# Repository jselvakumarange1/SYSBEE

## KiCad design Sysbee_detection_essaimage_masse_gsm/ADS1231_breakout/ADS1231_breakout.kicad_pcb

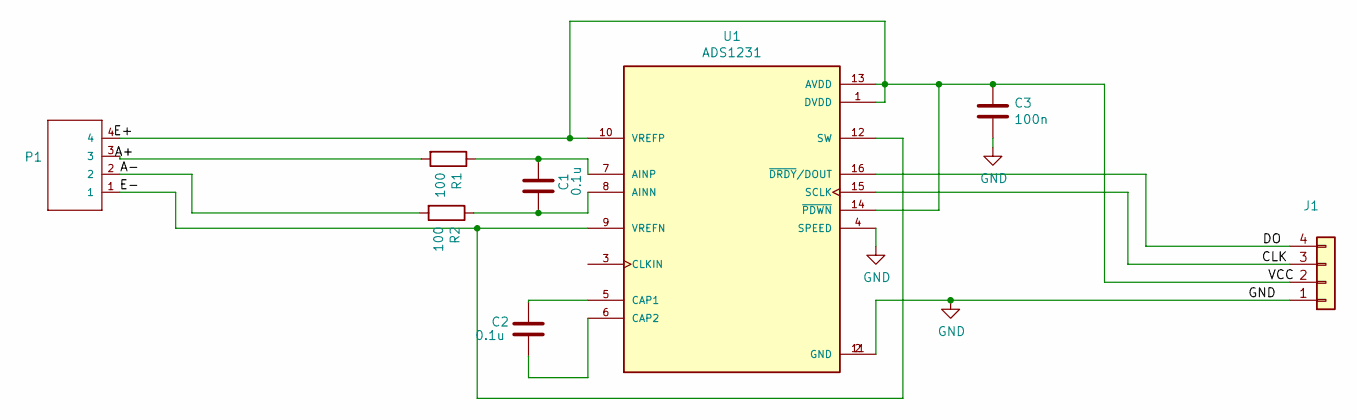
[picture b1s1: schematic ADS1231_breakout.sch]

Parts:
C1: 0.1u; C_1206_3216Metric
C2: 0.1u; C_1210_3225Metric
C3: 100n; C_1210_3225Metric
J1: FanPinHeader_1x04_P2.54mm_Vertical
P1: FanPinHeader_1x04_P2.54mm_Vertical
R1, R2: 100; R_1206_3216Metric
U1: ADS1231; SO-16_3.9x9.9mm_P1.27mm

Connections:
/A+: P1.3, R1.2
/A-: P1.2, R2.2
/CLK: J1.3, U1.15 (SCLK)
/DO: J1.4, U1.16 (~DRDY~/DOUT)
/E+: C3.1, J1.2, P1.4, U1.1 (DVDD), U1.10 (VREFP), U1.13 (AVDD), U1.14 (~PDWN)
/E-: P1.1, U1.9 (VREFN), U1.12 (SW)
GND: C3.2, J1.1, U1.2 (GND), U1.4 (SPEED), U1.11 (GND)
unnamed: C1.1, R1.1, U1.7 (AINP)
unnamed: C1.2, R2.1, U1.8 (AINN)
unnamed: C2.1, U1.5 (CAP1)
unnamed: C2.2, U1.6 (CAP2)

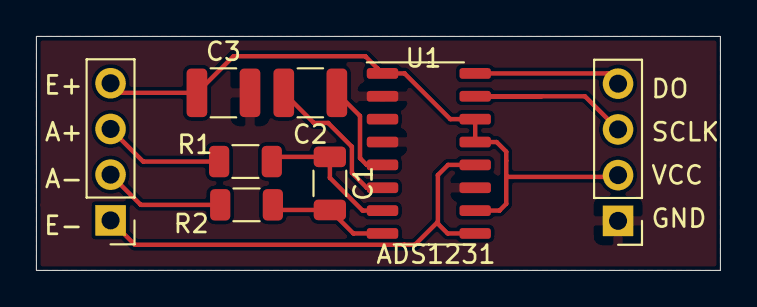
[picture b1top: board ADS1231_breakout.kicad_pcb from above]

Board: 2 copper layers, 38.0 x 13.0 mm, 8 parts (0 on the bottom side), 11 nets.

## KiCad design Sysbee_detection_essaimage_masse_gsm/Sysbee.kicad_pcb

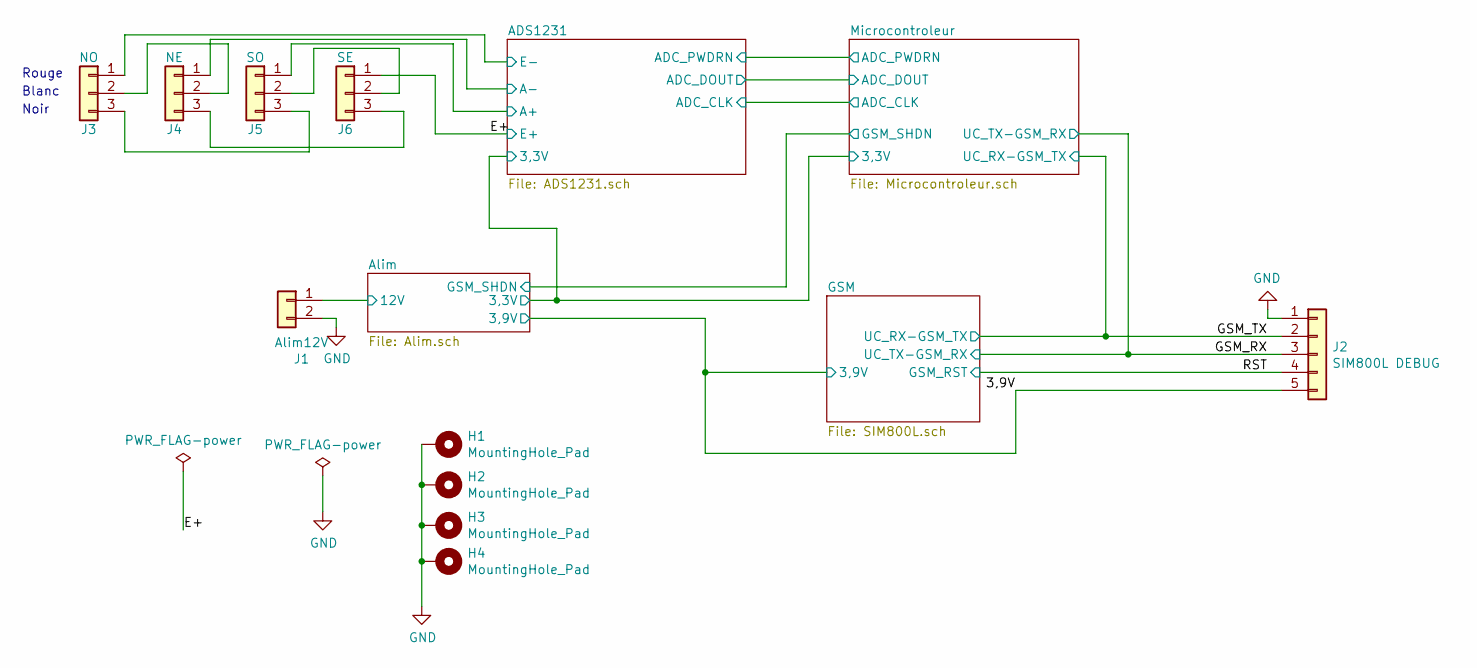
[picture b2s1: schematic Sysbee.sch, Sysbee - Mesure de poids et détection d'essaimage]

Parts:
H1, H2, H3, H4: MountingHole_Pad; Arduino_1pin
J1: Alim12V; PhoenixContact_MC_1,5_2-G-3.5_1x02_P3.50mm_Horizontal
J2: SIM800L DEBUG; PinHeader_1x05_P2.54mm_Vertical
J3: NO; JST_PH_B3B-PH-K_1x03_P2.00mm_Vertical
J4: NE; JST_PH_B3B-PH-K_1x03_P2.00mm_Vertical
J5: SO; JST_PH_B3B-PH-K_1x03_P2.00mm_Vertical
J6: SE; JST_PH_B3B-PH-K_1x03_P2.00mm_Vertical

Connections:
/3,9V: J2.5; also elsewhere on the board
/ADS1231/A+: J5.1; also elsewhere on the board
/ADS1231/A-: J4.1; also elsewhere on the board
/ADS1231/E-: J3.1; also elsewhere on the board
/Alim/12V: J1.1; also elsewhere on the board
/E+: J6.1; also elsewhere on the board
/GSM_RX: J2.3; also elsewhere on the board
/GSM_TX: J2.2; also elsewhere on the board
/RST: J2.4; also elsewhere on the board
GND: H1.1, H2.1, H3.1, H4.1, J1.2, J2.1; also elsewhere on the board
unnamed: J3.2, J4.2
unnamed: J3.3, J5.3
unnamed: J4.3, J6.3
unnamed: J5.2, J6.2

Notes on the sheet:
Rouge
Blanc
Noir

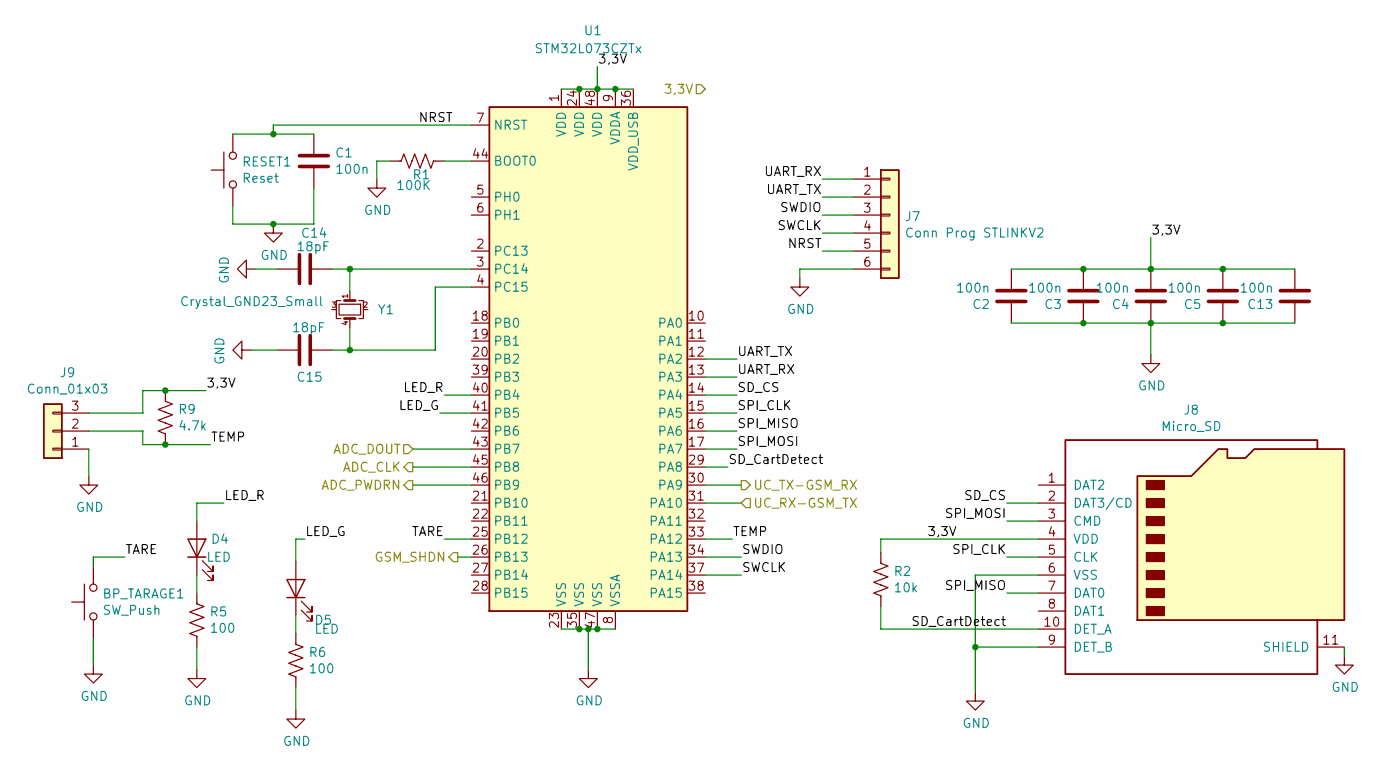
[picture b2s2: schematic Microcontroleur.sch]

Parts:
BP_TARAGE1: SW_Push; SW_SPST_TL3305C
C1, C2, C3, C4, C5, C13: 100n; C_1206_3216Metric
C14, C15: 18pF; C_0805_2012Metric
D4, D5: LED; LED_1206_3216Metric
J7: Conn Prog STLINKV2; Micro-match_6
J8: Micro_SD; 504077-1891
J9: Conn_01x03; JST_PH_B3B-PH-K_1x03_P2.00mm_Vertical
R1: 100K; R_1206_3216Metric
R2: 10k; R_1206_3216Metric
R5, R6: 100; R_1206_3216Metric
R9: 4.7k; R_1206_3216Metric
RESET1: Reset; SW_SPST_TL3305C
U1: STM32L073CZTx; LQFP-48_7x7mm_P0.5mm
Y1: Crystal_GND23_Small; Crystal_SMD_SeikoEpson_MC156-4Pin_7.1x2.5mm

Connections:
/ADS1231/ADC_CLK: U1.45 (PB8); also elsewhere on the board
/ADS1231/ADC_DOUT: U1.43 (PB7); also elsewhere on the board
/ADS1231/ADC_PWDRN: U1.46 (PB9); also elsewhere on the board
/Alim/GSM_SHDN: U1.26 (PB13); also elsewhere on the board
/E+: C2.2, C3.2, C4.2, C5.2, C13.2, J8.4 (VDD), J9.3, R2.1, R9.1, U1.1 (VDD), U1.9 (VDDA), U1.24 (VDD), U1.36 (VDD_USB), U1.48 (VDD); also elsewhere on the board
/GSM_RX: U1.30 (PA9); also elsewhere on the board
/GSM_TX: U1.31 (PA10); also elsewhere on the board
/Microcontroleur/LED_G: D5.2 (A), U1.41 (PB5)
/Microcontroleur/LED_R: D4.2 (A), U1.40 (PB4)
/Microcontroleur/NRST: C1.1, J7.5, RESET1.2, U1.7 (NRST)
/Microcontroleur/SD_CS: J8.2 (DAT3/CD), U1.14 (PA4)
/Microcontroleur/SD_CartDetect: J8.10 (DET_A), R2.2, U1.29 (PA8)
/Microcontroleur/SPI_CLK: J8.5 (CLK), U1.15 (PA5)
/Microcontroleur/SPI_MISO: J8.7 (DAT0), U1.16 (PA6)
/Microcontroleur/SPI_MOSI: J8.3 (CMD), U1.17 (PA7)
/Microcontroleur/SWCLK: J7.4, U1.37 (PA14)
/Microcontroleur/SWDIO: J7.3, U1.34 (PA13)
/Microcontroleur/TARE: BP_TARAGE1.2, U1.25 (PB12)
/Microcontroleur/TEMP: J9.2, R9.2, U1.33 (PA12)
/Microcontroleur/UART_RX: J7.1, U1.13 (PA3)
/Microcontroleur/UART_TX: J7.2, U1.12 (PA2)
GND: BP_TARAGE1.1, C1.2, C2.1, C3.1, C4.1, C5.1, C13.1, C14.2, C15.2, J7.6, J8.6 (VSS), J8.9 (DET_B), J8.11 (SHIELD), J9.1, R1.1, R5.2, R6.2, RESET1.1, U1.8 (VSSA), U1.23 (VSS), U1.35 (VSS), U1.47 (VSS); also elsewhere on the board
unnamed: C14.1, U1.3 (PC14), Y1.1
unnamed: C15.1, U1.4 (PC15), Y1.4
unnamed: D4.1 (K), R5.1
unnamed: D5.1 (K), R6.1
unnamed: R1.2, U1.44 (BOOT0)

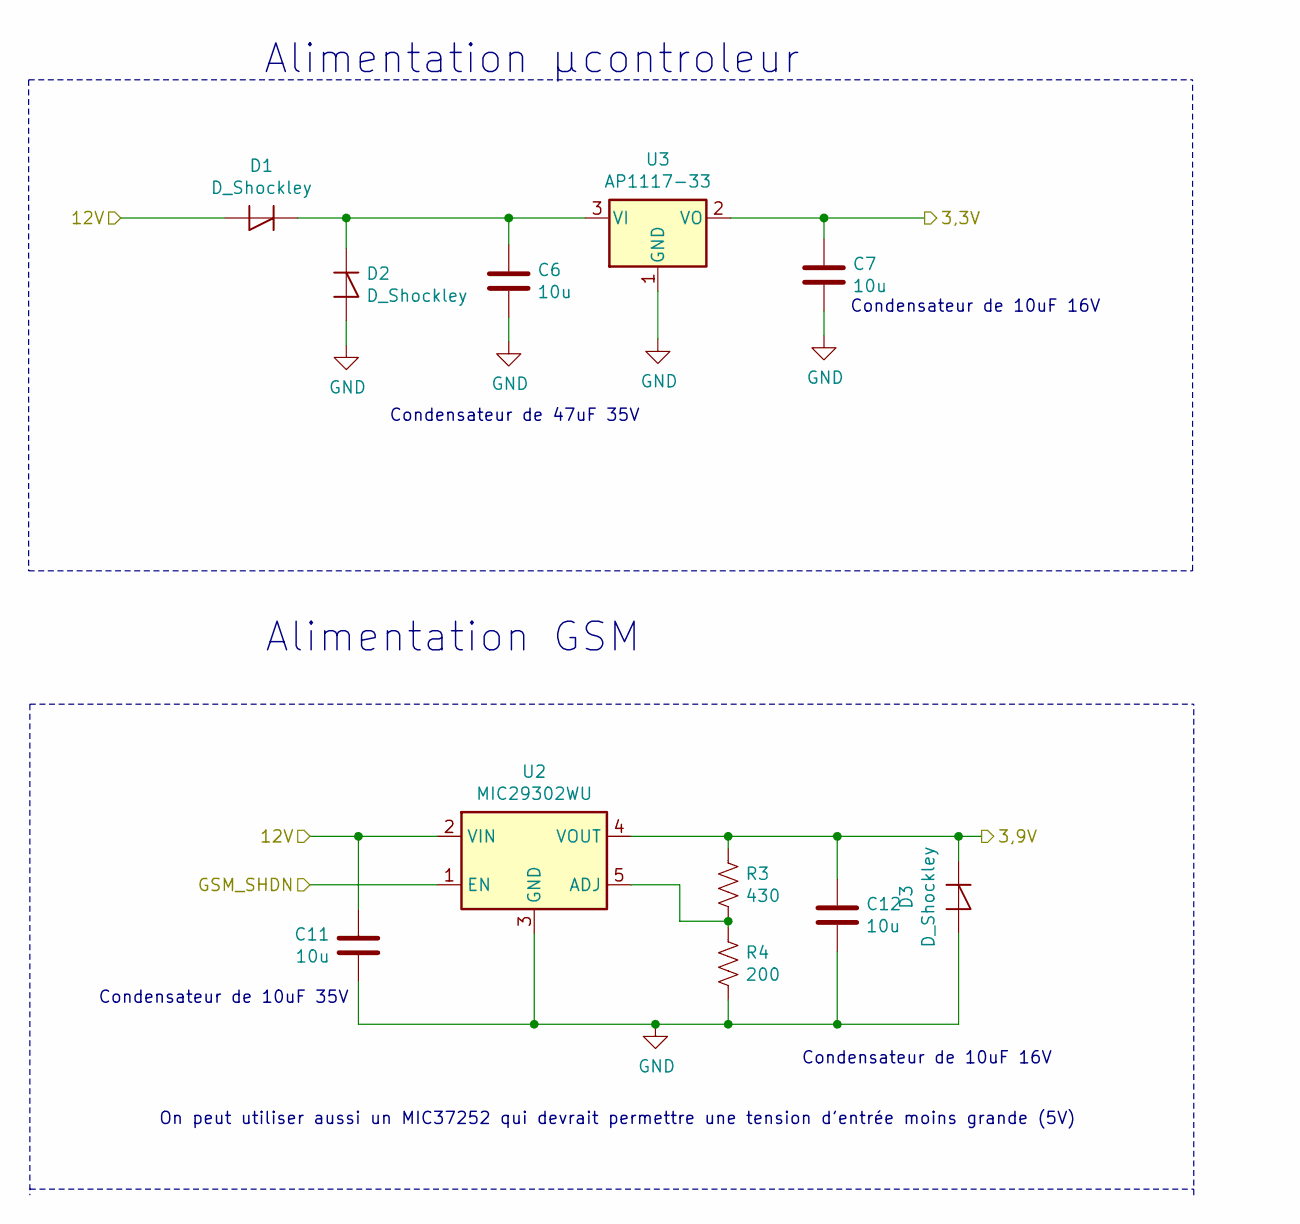
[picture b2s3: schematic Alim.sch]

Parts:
C6, C11: 10u; CP_EIA-6032-15_Kemet-U
C7, C12: 10u; CP_EIA-3528-21_Kemet-B
D1, D2, D3: D_Shockley; D_SOD-123
R3: 430; R_1206_3216Metric
R4: 200; R_1206_3216Metric
U2: MIC29302WU; TO-263-5_TabPin3
U3: AP1117-33; SOT-223-3_TabPin2

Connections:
/3,9V: C12.1, D3.1 (K), R3.1, U2.4 (VOUT); also elsewhere on the board
/Alim/12V: C11.2, D1.2 (A), U2.2 (VIN); also elsewhere on the board
/Alim/GSM_SHDN: U2.1 (EN); also elsewhere on the board
/E+: C7.1, U3.2 (VO); also elsewhere on the board
GND: C6.2, C7.2, C11.1, C12.2, D2.2 (A), D3.2 (A), R4.2, U2.3 (GND), U3.1 (GND); also elsewhere on the board
unnamed: C6.1, D1.1 (K), D2.1 (K), U3.3 (VI)
unnamed: R3.2, R4.1, U2.5 (ADJ)

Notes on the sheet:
Alimentation µcontroleur
Alimentation GSM
Condensateur de 10uF 35V
Condensateur de 10uF 16V
Condensateur de 47uF 35V
On peut utiliser aussi un MIC37252 qui devrait permettre une tension d'entrée moins grande (5V)

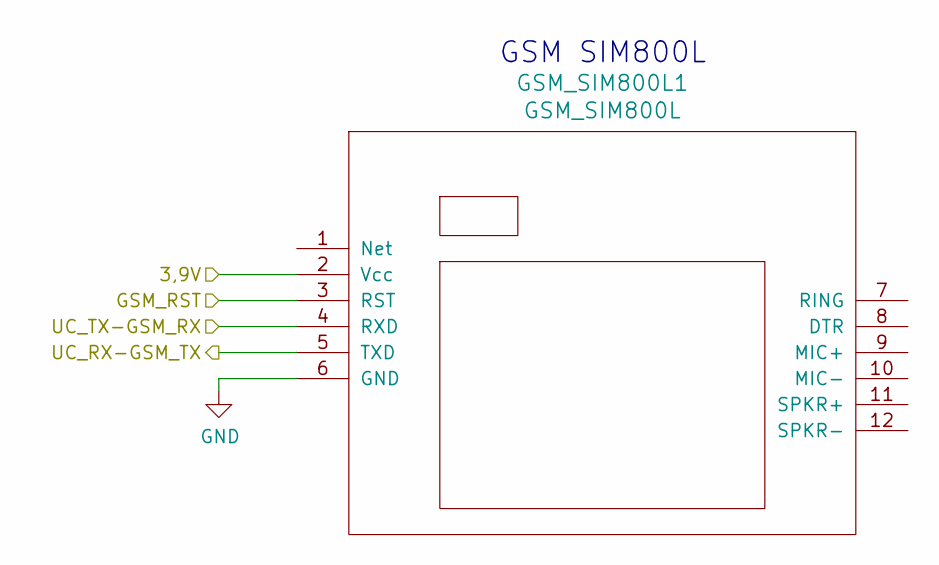
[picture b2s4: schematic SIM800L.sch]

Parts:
GSM_SIM800L1: GSM_SIM800L; SIM800L

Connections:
/3,9V: GSM_SIM800L1.2 (Vcc); also elsewhere on the board
/GSM_RX: GSM_SIM800L1.4 (RXD); also elsewhere on the board
/GSM_TX: GSM_SIM800L1.5 (TXD); also elsewhere on the board
/RST: GSM_SIM800L1.3 (RST); also elsewhere on the board
GND: GSM_SIM800L1.6 (GND); also elsewhere on the board

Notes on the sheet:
GSM SIM800L

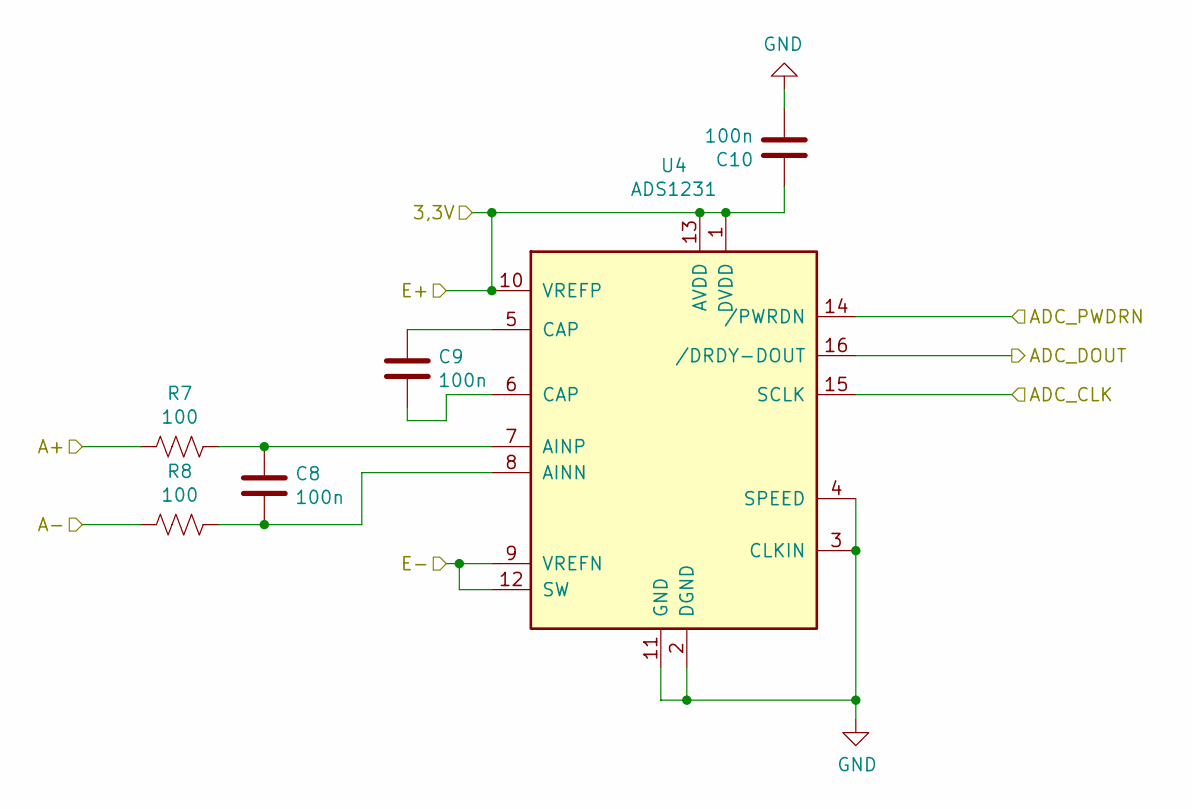
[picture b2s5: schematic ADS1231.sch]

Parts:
C8, C9, C10: 100n; C_1206_3216Metric
R7, R8: 100; R_1206_3216Metric
U4: ADS1231; SOIC-16_3.9x9.9mm_P1.27mm

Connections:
/ADS1231/A+: R7.2; also elsewhere on the board
/ADS1231/A-: R8.2; also elsewhere on the board
/ADS1231/ADC_CLK: U4.15 (SCLK); also elsewhere on the board
/ADS1231/ADC_DOUT: U4.16 (/DRDY-DOUT); also elsewhere on the board
/ADS1231/ADC_PWDRN: U4.14 (/PWRDN); also elsewhere on the board
/ADS1231/E-: U4.9 (VREFN), U4.12 (SW); also elsewhere on the board
/E+: C10.1, U4.1 (DVDD), U4.10 (VREFP), U4.13 (AVDD); also elsewhere on the board
GND: C10.2, U4.2 (DGND), U4.3 (CLKIN), U4.4 (SPEED), U4.11 (GND); also elsewhere on the board
unnamed: C8.1, R7.1, U4.7 (AINP)
unnamed: C8.2, R8.1, U4.8 (AINN)
unnamed: C9.1, U4.5 (CAP)
unnamed: C9.2, U4.6 (CAP)

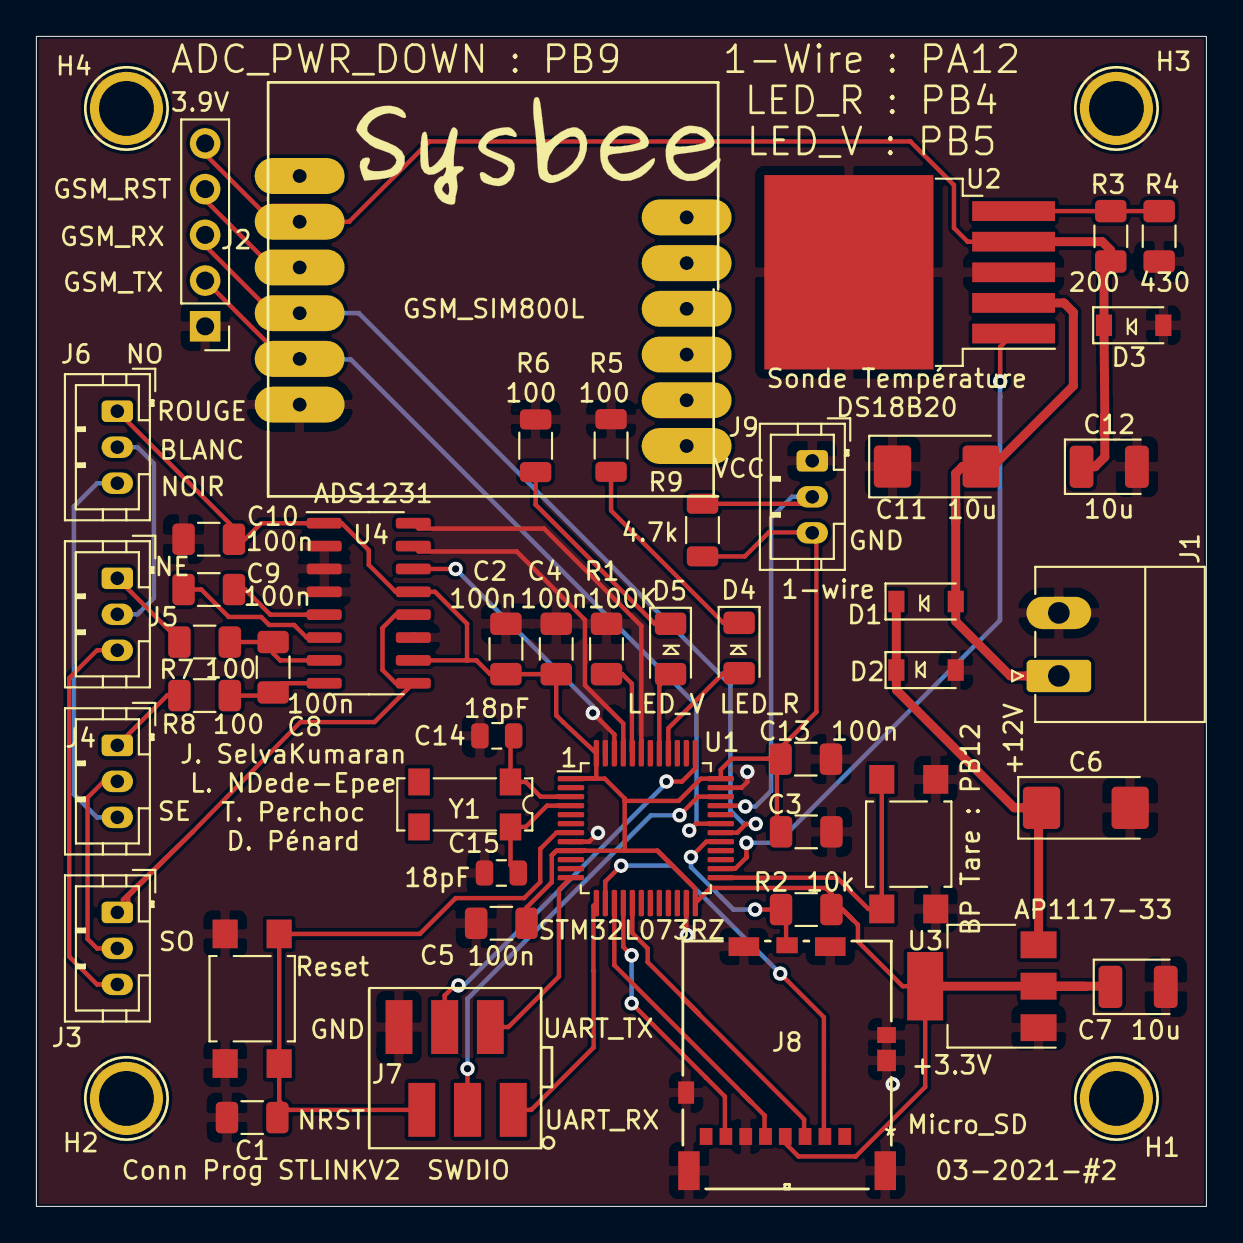
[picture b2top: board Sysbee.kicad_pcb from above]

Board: 2 copper layers, 65.0 x 65.0 mm, 50 parts (0 on the bottom side), 43 nets.

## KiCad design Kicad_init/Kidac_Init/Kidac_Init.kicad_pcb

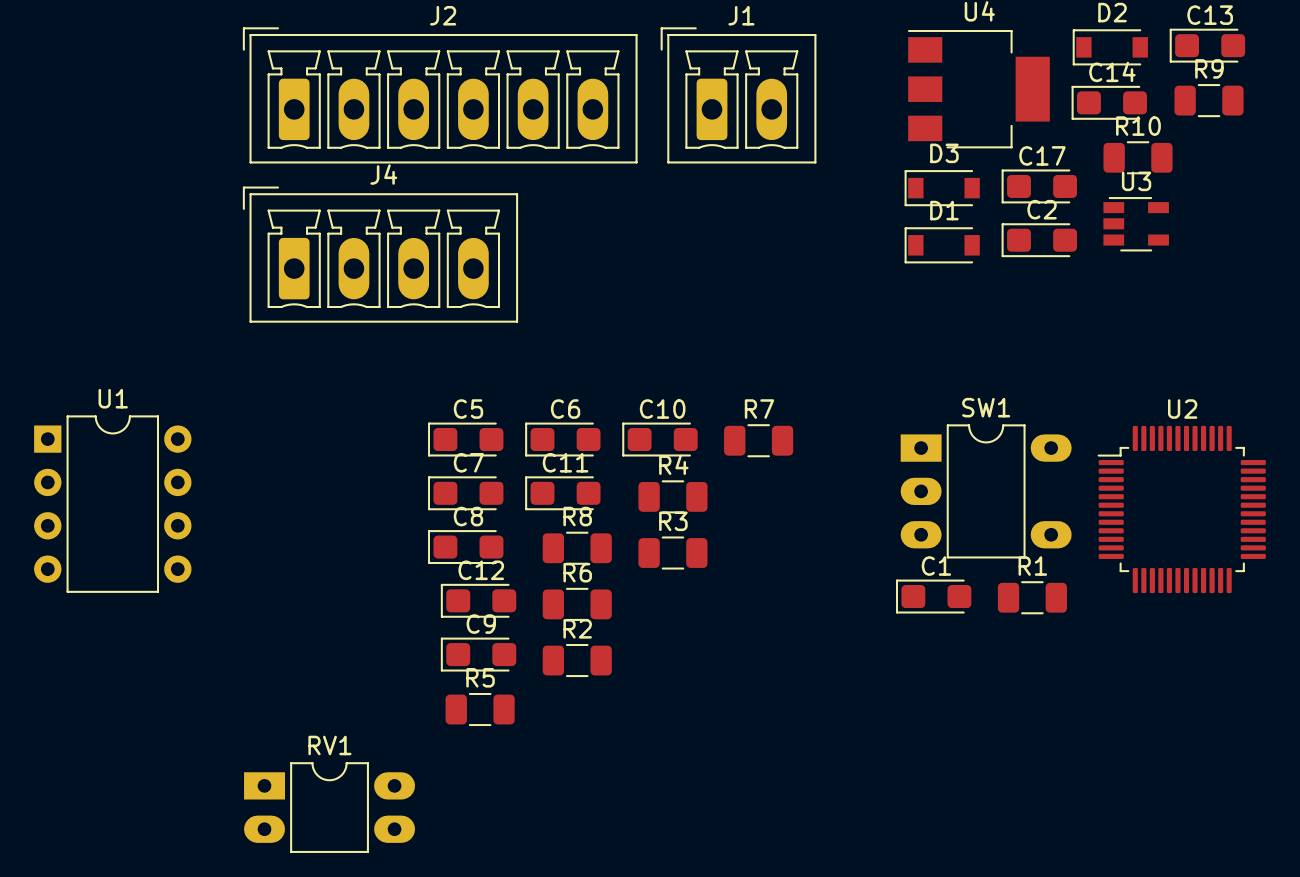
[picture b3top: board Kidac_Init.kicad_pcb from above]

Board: 2 copper layers, 35 parts (0 on the bottom side), 23 nets, no tracks yet.

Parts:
C1, C7, C10: 100n; CP_EIA-3216-18_Kemet-A
C2, C13, C14: 10uF; CP_EIA-3216-18_Kemet-A
C5: 1u; CP_EIA-3216-18_Kemet-A
C6, C9, C12: 10u; CP_EIA-3216-18_Kemet-A
C8: 330n; CP_EIA-3216-18_Kemet-A
C11: 220p; CP_EIA-3216-18_Kemet-A
C17: 1uF; CP_EIA-3216-18_Kemet-A
D1, D2, D3: D_Schottky; D_SOD-123
J1: Conn_01x02; PhoenixContact_MCV_1,5_2-G-3.5_1x02_P3.50mm_Vertical
J2: Conn_01x06; PhoenixContact_MCV_1,5_6-G-3.5_1x06_P3.50mm_Vertical
J4: Conn_01x04; PhoenixContact_MCV_1,5_4-G-3.5_1x04_P3.50mm_Vertical
R1: 100k; R_1206_3216Metric
R2: 1k; R_1206_3216Metric
R3, R5: 2k; R_1206_3216Metric
R4, R6: 22k; R_1206_3216Metric
R7: 15k; R_1206_3216Metric
R8: 150k; R_1206_3216Metric
R9, R10: 4.7k; R_1206_3216Metric
RV1: 100k; DIP-4_W7.62mm_LongPads
SW1: SW_Push; DIP-5-6_W7.62mm_LongPads
U1: TLV2372; DIP-8_W7.62mm
U2: STM32L073CZTx; LQFP-48_7x7mm_P0.5mm
U3: LT1764; TSOT-23-5
U4: AP1117-33; SOT-223-3_TabPin2

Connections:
+3V0: C9.1, C10.1, R2.1, R4.1, U1.8
/GSM/TX: J2.1, U2.13
/alim/3.3V: C2.1, U4.2
/alim/3V8: C14.1, D3.1, R9.1, U3.3, U3.4, U3.5
/alim/12V: C13.1, D1.2, J1.1, J4.3
/preampli_micro/micro+: C6.1, J4.1, R3.2
/µcontroleur/NRST: C1.1, J2.5, SW1.2, U2.7
/µcontroleur/SWCLK: J2.4, U2.37
/µcontroleur/SWDID: J2.3, U2.34
/µcontroleur/UART_TX: J2.2, U2.12
GND: C1.2, C2.2, C5.1, C7.2, C9.2, C10.2, C13.2, C14.2, C17.2, D2.2, D3.2, J1.2, J2.6, J4.2, R1.1, R6.2, R10.2, SW1.1, U1.4, U2.8, U2.23, U2.35, U2.47, U3.1, U4.1
unnamed: C5.2, R2.2, R3.1
unnamed: C6.2, R5.1
unnamed: C7.1, R4.2, R6.1, U1.3, U1.5
unnamed: C8.1, RV1.2, RV1.3, U1.1
unnamed: C8.2, R7.1
unnamed: C11.1, R7.2, R8.1, U1.6
unnamed: C11.2, C12.1, R8.2, U1.7
unnamed: C17.1, D1.1, D2.1, U4.3
unnamed: R1.2, U2.44
unnamed: R5.2, RV1.1, U1.2
unnamed: R9.2, R10.1
unnamed: U2.1, U2.9, U2.24, U2.36, U2.48

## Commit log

2021-03-02 Create SOUNDBEE
2021-03-09 placement et routage, reste à redessiner un peu les pistes et rajouter les écritures F.Silks
2021-03-09 placement et routage ok
2021-03-09 du ménage de fait pas de mal de temps en temps

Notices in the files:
parts and their libraries:
Copyright 2016 Accelerated Designs. All rights reserved.
